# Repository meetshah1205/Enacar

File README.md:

# 🛞 Enacar — The First Movement (a.k.a. I Just Wanted This Thing to Move)

## 📘 Overview

Alright listen up. This isn’t some NASA-grade AI rover (yet) — it’s **Enacar**, and this is version 0.0000001a.  
The goal? Make Motor A spin. That’s it. That’s the tweet.

This whole thing is less “professional engineering” and more “I’m fighting copper wires and battery packs with the rage of Zeus.”  
If you're reading this for inspiration — buckle up, 'cause this ride is sponsored by procrastination, taped wires, and raw willpower.

## 🧰 Hardware Requirements (a.k.a. What's in the Bag?)

- Arduino Uno (my baby)  
- L293D Motor Driver IC (the actual hero here)  
- 1 DC Motor (Motor A, the chosen one)  
- Breadboard (a.k.a. the plastic jungle)  
- Jumper wires (which may or may not work depending on their mood)  
- 6 AA batteries + holder (Duracell or riot)  
- Electrical tape (used more than it should be)  
- USB cable (power from the gods)  
- That one cousin you call when it doesn’t upload

## ⚙️ Circuit Description (aka “what the hell is going on?”)

So, Arduino is the brain. L293D is the muscles. Batteries are the protein shake.  
The brain says “move,” the muscles do it, and the protein keeps it alive.

We only wired **Motor A** — baby steps, alright?

### Wiring Table

| Arduino Pin | L293D Pin | What It Does                          |
|-------------|-----------|----------------------------------------|
| D10         | 1 (ENA)   | Gives motor permission to vibe ✅  
| D9          | 2 (IN1)   | Tells it where to spin ✅  
| D8          | 7 (IN2)   | Confuses the motor the other way ✅  
| 5V          | 16        | Brains need juice ✅  
| GND         | GND       | So everything shares trauma ✅  
| Motor A     | 3 & 6     | Motor output channels ✅  
| Battery (+) | 8         | Where the power party starts ✅  
| Battery (–) | GND       | Don’t forget this or NOTHING works ✅  

## 🔌 Circuit Diagram

🧠 Legend:  
- Green: Motor (obviously)  
- Orange: Direction & enable sauce  
- Red: Life juice ⚡  
- Black: Emotional grounding 🌑  

## 🧪 The Code (the magic spell)

```cpp
int enA = 10;
int in1 = 9;
int in2 = 8;

void setup() {
  pinMode(enA, OUTPUT);
  pinMode(in1, OUTPUT);
  pinMode(in2, OUTPUT);
  Serial.begin(9600);
  Serial.println("Enacar booting... 🧠⚙️");
}

void loop() {
  Serial.println("Motor A: FORWARD");
  digitalWrite(in1, HIGH);
  digitalWrite(in2, LOW);
  analogWrite(enA, 200);
  delay(2000);

  Serial.println("Motor A: STOP");
  analogWrite(enA, 0);
  delay(1000);

  Serial.println("Motor A: REVERSE");
  digitalWrite(in1, LOW);
  digitalWrite(in2, HIGH);
  analogWrite(enA, 200);
  delay(2000);

  Serial.println("Motor A: STOP");
  analogWrite(enA, 0);
  delay(1000);
}
```

## 💡 Learn From My Pain

- Don’t power motors from Arduino’s 5V pin unless you wanna see it faint.  
- Always **share ground** or the circuit gets ✨emotional✨.  
- Wires won’t strip themselves — you *will* become a caveman eventually.  
- The barrel jack? Lies. Cut it. Yeet it. Never trust it.  
- Electrical tape is now your soulmate. Stick to it. Literally.

## 😤 Lore Dump (Because Yes)

It all started with a wooden board, some motors, and existential dread. I stared into the void. It stared back.  
Then I saw the wires. The cursed, stiff, glued-worse-than-your-ex wires.

Copper? **Nonexistent.** I had to perform a full-scale **surgical extraction** with scissors, hope, and 0.3% knowledge of physics.  
But I struck it. I found copper. And in that moment — I became GOD.

Batteries were acquired. Connections made. USB plugged. Sketch uploaded.  
**AND IT MOVED.**  
One wheel. One motor. One glorious rotation.

And that's where the Enacar began. 😤🛞

---

📁 This is Enacar: Day 1. The revolution will not be stable. But it'll be cool as hell.

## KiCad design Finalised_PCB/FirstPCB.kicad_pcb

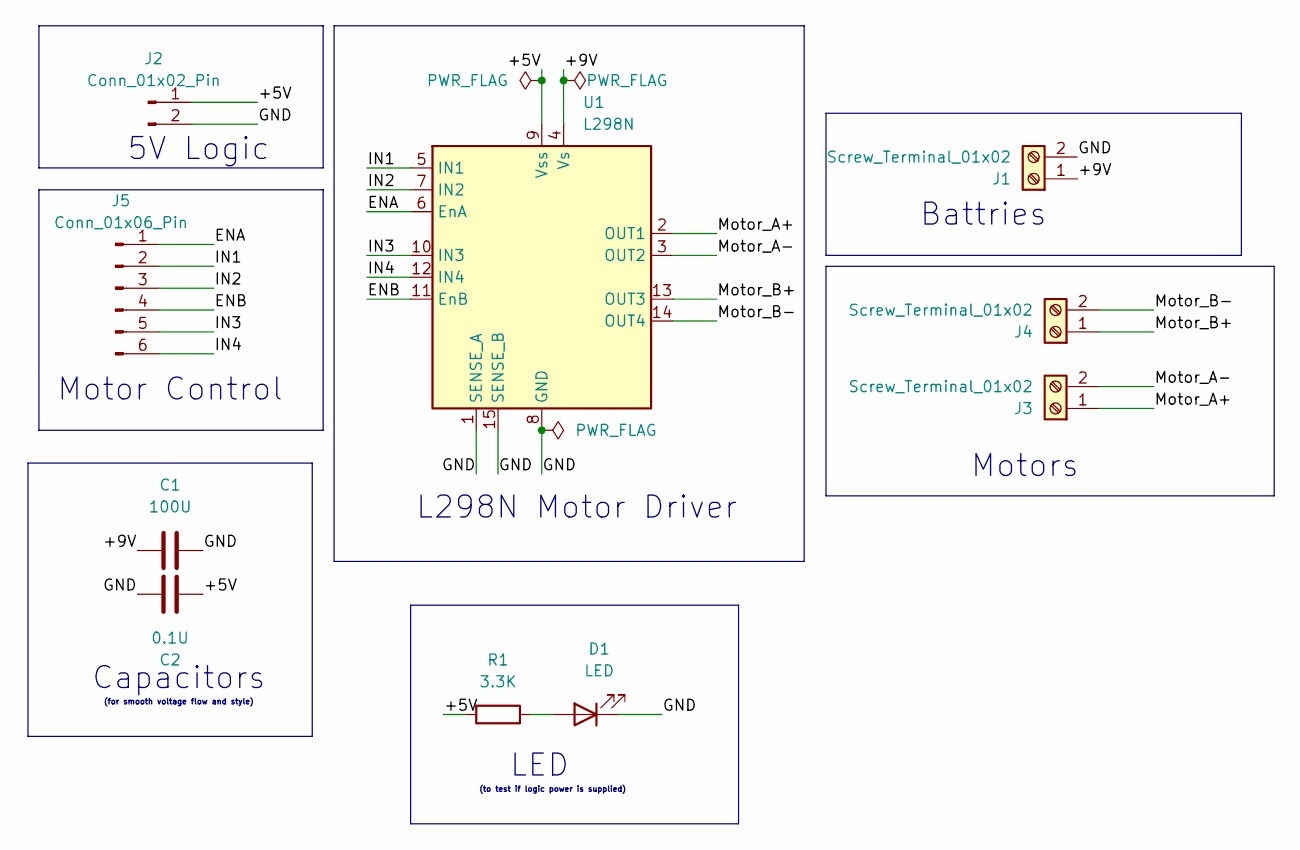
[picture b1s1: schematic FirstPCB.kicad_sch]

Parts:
C1: 100U; C_Disc_D3.0mm_W1.6mm_P2.50mm
C2: 0.1U; CP_Radial_D8.0mm_P3.50mm
D1: LED; LED_D5.0mm
J1, J3, J4: Screw_Terminal_01x02; TerminalBlock_Phoenix_MKDS-3-2-5.08_1x02_P5.08mm_Horizontal
J2: Conn_01x02_Pin; PinHeader_1x02_P2.54mm_Vertical
J5: Conn_01x06_Pin; PinHeader_1x06_P2.54mm_Vertical
R1: 3.3K; R_Axial_DIN0207_L6.3mm_D2.5mm_P7.62mm_Horizontal
U1: L298N; TO-220-15_P2.54x5.08mm_StaggerOdd_Lead4.58mm_Vertical

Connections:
/+5V: C2.1, J2.1, R1.1, U1.9 (Vss)
/+9V: C1.1, J1.1, U1.4 (Vs)
/ENA: J5.1, U1.6 (EnA)
/ENB: J5.4, U1.11 (EnB)
/GND: C1.2, C2.2, D1.1 (K), J1.2, J2.2, U1.1 (SENSE_A), U1.8 (GND), U1.15 (SENSE_B)
/IN1: J5.2, U1.5 (IN1)
/IN2: J5.3, U1.7 (IN2)
/IN3: J5.5, U1.10 (IN3)
/IN4: J5.6, U1.12 (IN4)
/Motor_A+: J3.1, U1.2 (OUT1)
/Motor_A-: J3.2, U1.3 (OUT2)
/Motor_B+: J4.1, U1.13 (OUT3)
/Motor_B-: J4.2, U1.14 (OUT4)
unnamed: D1.2 (A), R1.2

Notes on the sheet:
Capacitors
(to test if logic power is supplied)
5V Logic
Motor Control
(for smooth voltage flow and style)
Battries
LED
Motors
L298N Motor Driver

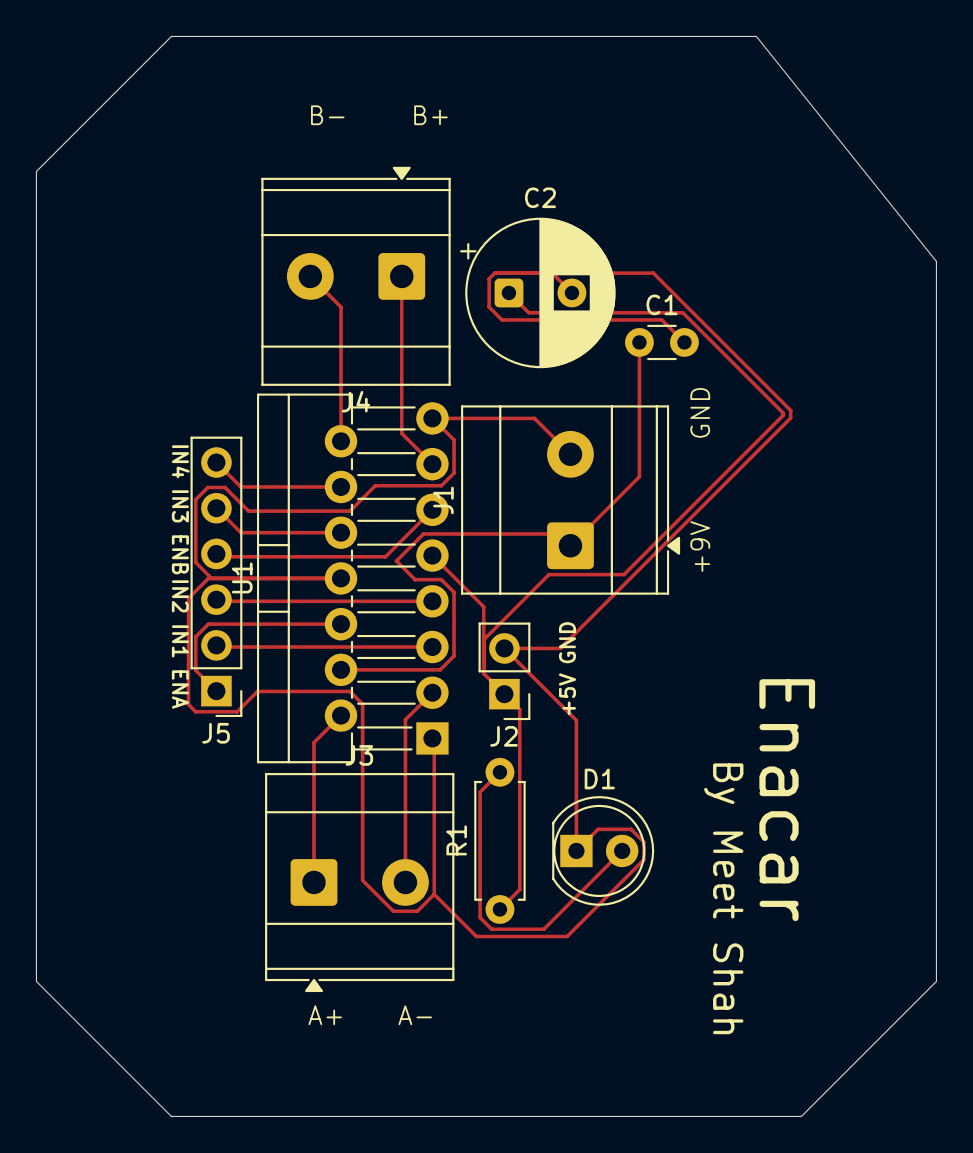
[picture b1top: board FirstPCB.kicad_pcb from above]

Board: 2 copper layers, 50.0 x 60.0 mm, 10 parts (0 on the bottom side), 14 nets.

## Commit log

2025-07-12 WE HAVE MOVEMENT
2025-09-08 PCB
    Designed a PCB and a schematic for the control board using L298N, 9V supply and Arduino
2025-09-15 Added silkscreen designs and labels
2025-09-16 Made huge changes
    Made the traces proper thickness (motor and 9V traces 2.0mm, logic 0.5mm etc.).
    Added professional-looking silkscreens.
    Now it looks professional, cool and something probably banned in airports :)
